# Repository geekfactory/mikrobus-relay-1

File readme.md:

# mikroBUS compatible relay module (single channel)

This is simple but useful relay module compatible with mikroBUS sockets. It was designed using Autodesk EAGLE free edition.

The relay is a G5-LE from Omron rated for 10A and up to 250 VAC. This module includes all the components to drive the coil using digital signals. An LED provides visual feedback when the coil is energized.

The relay module is designed to be activated with a HIGH level from the microcontroller.

For more information about the design of this module please check the following link:

* 

## Features and hardware details

* G5LE Omron relay can be used to switch AC or DC loads
* Up to 10 A and 250 VAC switching capability
* mikroBUS form factor can fit a wide variety of development boards
* Designed for 5 VDC coil relays (coil is driven with 5 volts)
* G5-LE can be exchanged for other relay with the same footprint
* LED indicator for relay status
* Activation signal hardwired to the CS pin but can be changed to the following pins using solder jumpers:
	* RST
	* PWM
	* INT

## Repository contents

1. __root__ - EAGLE Source files for the board
2. __/documents__ - Additional documentation, datasheets and assembly instructions
3. __/production__ - History of gerber files sent for production
4. __/extras__ - Technical drawings, mounting hardware and related accessories
4. __/firmware__ - Testing or definitive firmware for this board

## Hardware revisions

* 1.0 - First revision

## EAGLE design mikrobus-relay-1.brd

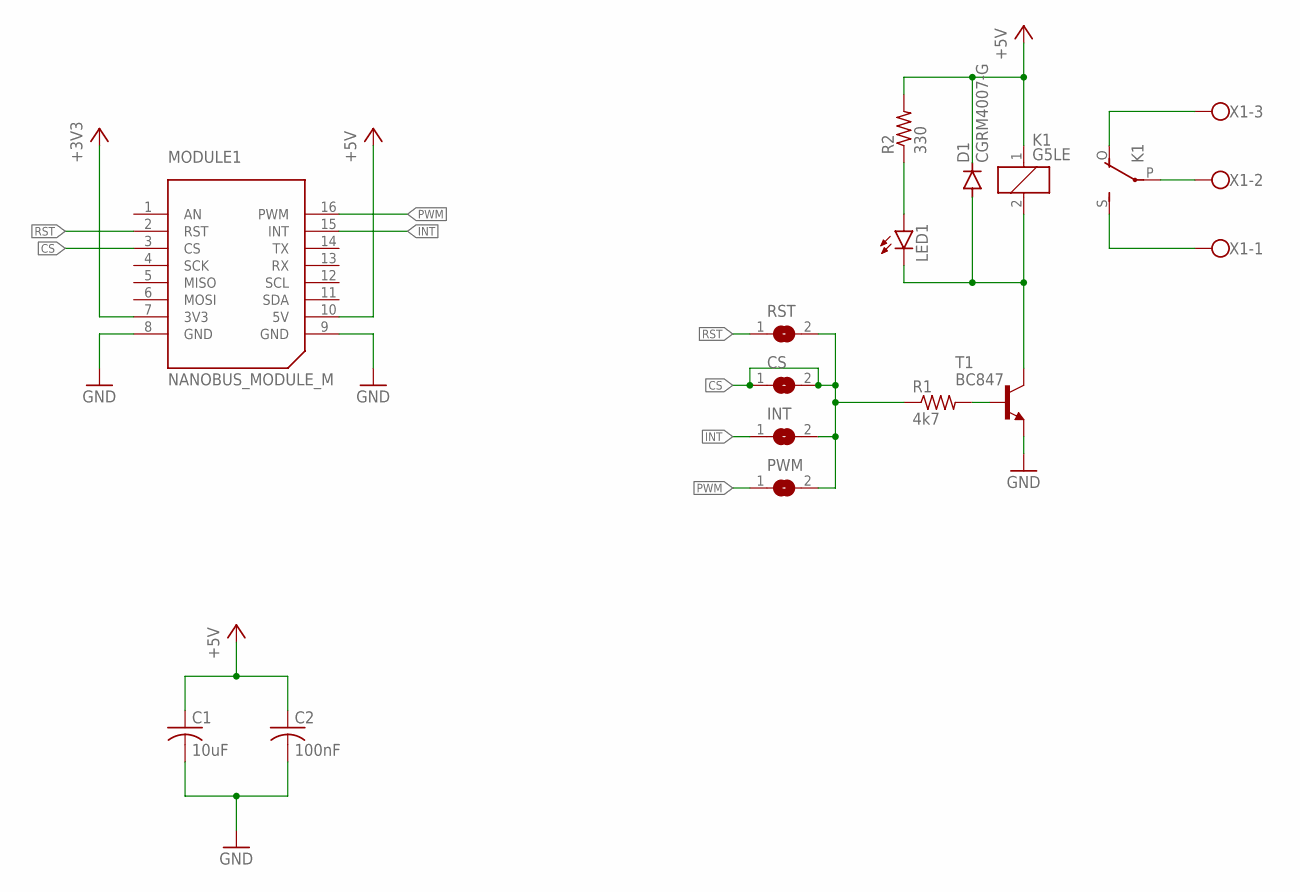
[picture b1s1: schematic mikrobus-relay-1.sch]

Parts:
C1: 10uF; C0805
C2: 100nF; C0805
CS: SJ
D1: CGRM4007-G; SOD-123_MINI-SMA
INT: SJ
K1: G5LE
LED1: LEDCHIPLED_0805; CHIPLED_0805
MODULE1: NANOBUS_MODULE_M; NANOBUS_MODULE_MIDDLE
PWM: SJ
R1: 4k7; R0805
R2: 330; R0805
RST: SJ
T1: BC847; SOT23
X1: SCREW-TERMINAL-3-5-0; SCREW-TERMINAL-5.0MM-3

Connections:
+3V3: MODULE1.7 (3V3)
+5V: C1.1, C2.1, D1.C, K1.1, MODULE1.10 (5V), R2.2
CS: CS.1, CS.2, INT.2, MODULE1.3 (CS), PWM.2, R1.1, RST.2
GND: C1.2, C2.2, MODULE1.8 (GND), MODULE1.9 (GND), T1.2 (E)
INT: INT.1, MODULE1.15 (INT)
unnamed: D1.A, K1.2, LED1.C, T1.3 (C)
unnamed: LED1.A, R2.1
unnamed: R1.2, T1.1 (B)
PWM: MODULE1.16 (PWM), PWM.1
RCOM: K1.P, X1.2
RNC: K1.O, X1.3
RNO: K1.S, X1.1
RST: MODULE1.2 (RST), RST.1

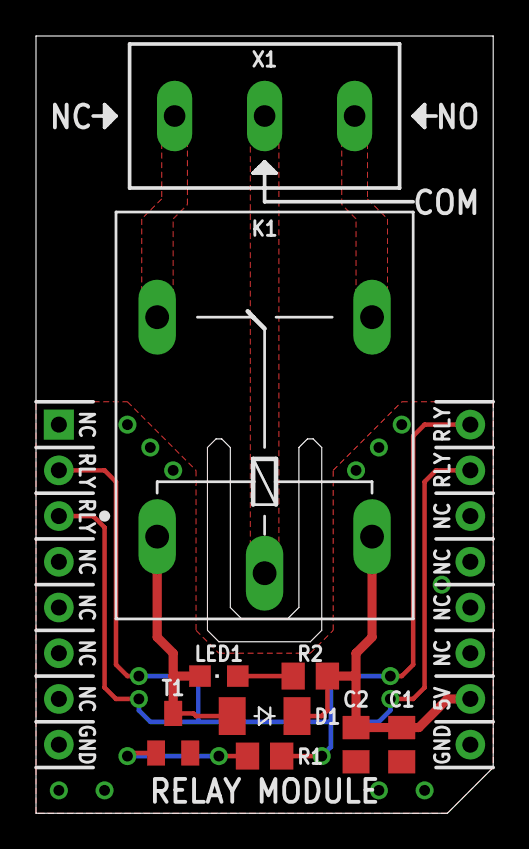
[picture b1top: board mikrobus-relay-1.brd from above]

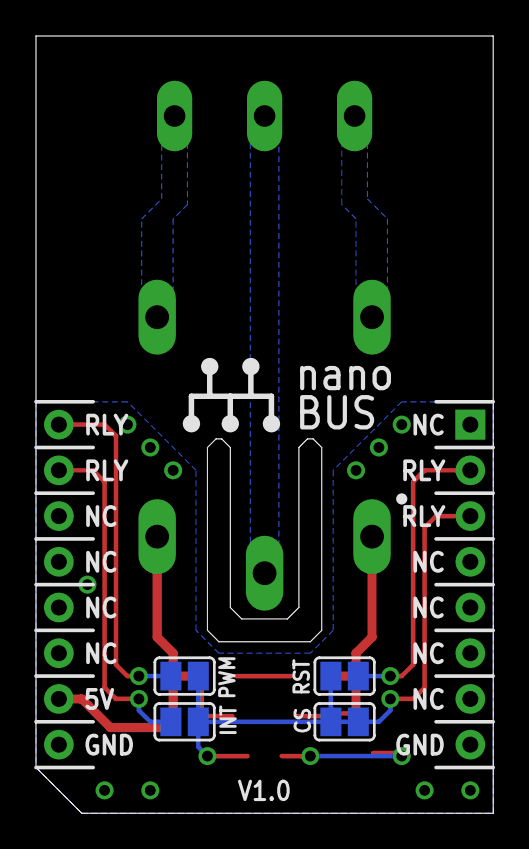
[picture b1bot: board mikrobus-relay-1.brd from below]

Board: 2 copper layers, 25.4 x 43.2 mm, 14 parts (4 on the bottom side), 12 nets.
